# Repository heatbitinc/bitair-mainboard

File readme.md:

# Heatbit Bitair Mainboard

The mining mainboard of the Heatbit Bitair air purifier. It carries a single
Bitmain **BM1370** Bitcoin mining ASIC and an **ESP32-S3**, and the heat from
the ASIC is used by the purifier.

The design is based on the open source
[bitaxeGamma](https://github.com/bitaxeorg/bitaxeGamma) by bitaxeorg. See [NOTICE.md](NOTICE.md) for the upstream revision
and the full list of changes.

## Status

| Revision | Date       | Status                         |
|----------|------------|--------------------------------|
| V1.22    | 2026-08-24 | Production, shipped in Bitair  |
| V1.11    | 2026-07-31 | Internal, debugging only       |
| V1.00    | 2026-07-10 | Internal, debugging only       |

See [CHANGELOG.md](CHANGELOG.md).

## Overview

- ASIC: Bitmain BM1370 (the chip used in the Antminer S21 Pro). It is not
  open source and is not sold individually. Upstream reports about
  1.2 TH/s per chip.
- Core power: TI TPS546D24A step-down converter for the ASIC core (VDD),
  same as bitaxeGamma.
- 5 V rail: an on-board step-down converter from the CN1 input (sheet
  `Power_15_5`, NDP1415QF controller).
- MCU: ESP32-S3-WROOM-1 (N16R8).
- Fan control and ASIC temperature: Microchip EMC2101.
- PCB: 4 layers, about 72.5 × 80.5 mm. KiCad 10 (the files no longer open in KiCad 9).

**Active cooling is mandatory.** The board is designed to run with the
purifier's heatsink and airflow. Running it without them will overheat the
ASIC.

## Connectors

### CN1: system connector (JST B10B-PHDSS, 2 mm, 10 pins)

This connector links the board to the rest of the air purifier.

| Pin | Net       | Description |
|-----|-----------|-------------|
| 1   | VBUS      | Power input. 15 V nominal; the input converter enables at about 12 V (see the notes on sheet `Power_15_5`). Protected by fuse F1 (3 A). |
| 2   | VBUS      | Power input, same as pin 1 |
| 3   | GND       | Ground |
| 4   | GND       | Ground |
| 5   | SCL (ext) | I2C clock for an external sensor (AHT20). Level-shifted by Q4 (2N7002) from the 3.3 V bus. Needs a pull-up on the external side. |
| 6   | LED       | ESP32 GPIO41, 3.3 V logic, direct |
| 7   | SDA (ext) | I2C data for an external sensor. Level-shifted by Q5 (2N7002). Needs a pull-up on the external side. |
| 8   | FAN       | ESP32 GPIO40 through the level shifter Q3 (2N7002, 5.1 kΩ pull-up to 3.3 V on the ESP32 side). Pulled low when GPIO40 is low; needs a pull-up on the external side. |
| 9   | B         | ESP32 GPIO39, 3.3 V logic, direct |
| 10  | FAN_PWM   | Fan PWM from the EMC2101, 10 kΩ pull-up to 5 V |

The ESP32 measures the VBUS voltage on GPIO6 through a 51 kΩ / 12 kΩ divider.

### J5: USB-C

USB 2.0 data to the ESP32-S3, used for flashing and logs. USB VBUS is **not
connected**: the board cannot be powered from USB.

### J1: programming header (not populated)

A 1.27 mm, 6-pin footprint: 3V3, TX, RX, GND, IO0, EN (ESP32 UART0 and boot).

## Repository contents

| Path | Contents |
|------|----------|
| `bitair-mainboard.kicad_pro` | KiCad 10 project |
| `*.kicad_sch` | Schematic: root sheet, `bm1370`, `power`, `Power_15_5`, `esp32`, `fan` |
| `bitair-mainboard.kicad_pcb` | PCB |
| `bitaxe.kicad_sym`, `bitaxe.pretty` | Symbol and footprint libraries from upstream bitaxe |
| `bitair.kicad_sym`, `bitair.pretty`, `Heatbit.kicad_sym`, `Heatbit.pretty` | Libraries added by Heatbit |
| `3d`, `3dshapes` | 3D models used by the PCB, see [THIRD_PARTY.md](THIRD_PARTY.md) |
| `OUTPUTS/` | Fabrication outputs for V1.22: Gerbers and drill files, BOM, pick-and-place, schematic PDF |

## Manufacturing

- Gerbers and drill files: `OUTPUTS/HB Bitair MainBoard V1.22 GBR/`
- BOM: `OUTPUTS/Assembly/BOM/` (xlsx and csv). The `LCSC` column lists the
  parts used in production. `Manufacturer`/`MPN` are filled where known.
  `Alt MPN`/`DigiKey` are the alternatives inherited from bitaxeGamma for
  parts that did not change.
- Pick-and-place: `OUTPUTS/Assembly/PnP/`
- Schematic PDF: `OUTPUTS/Assembly/Circuit Diagram/`

The BM1370 is not available from regular distributors.

See [building.md](building.md) for generating fabrication files and
[assembly.md](assembly.md) for hand-assembly tips from the bitaxe project.

## Firmware

The firmware is not part of this repository.

## Licence

Copyright (c) 2026 Heatbit Inc. Based on bitaxeGamma, copyright (c)
bitaxeorg.

This design is licensed under the
[CERN-OHL-S-2.0](LICENSE). If you distribute boards or modified designs based
on it, you must make your complete modified source available under the same
licence.

"Heatbit", "Bitair" and the Heatbit logo are trademarks of Heatbit Inc. and
are not covered by the licence. See [TRADEMARKS.md](TRADEMARKS.md) before
manufacturing boards from this design. Bitaxe is a trademark of bitaxeorg;
this is not an official Bitaxe product.

Third-party components and 3D models are listed in
[THIRD_PARTY.md](THIRD_PARTY.md).

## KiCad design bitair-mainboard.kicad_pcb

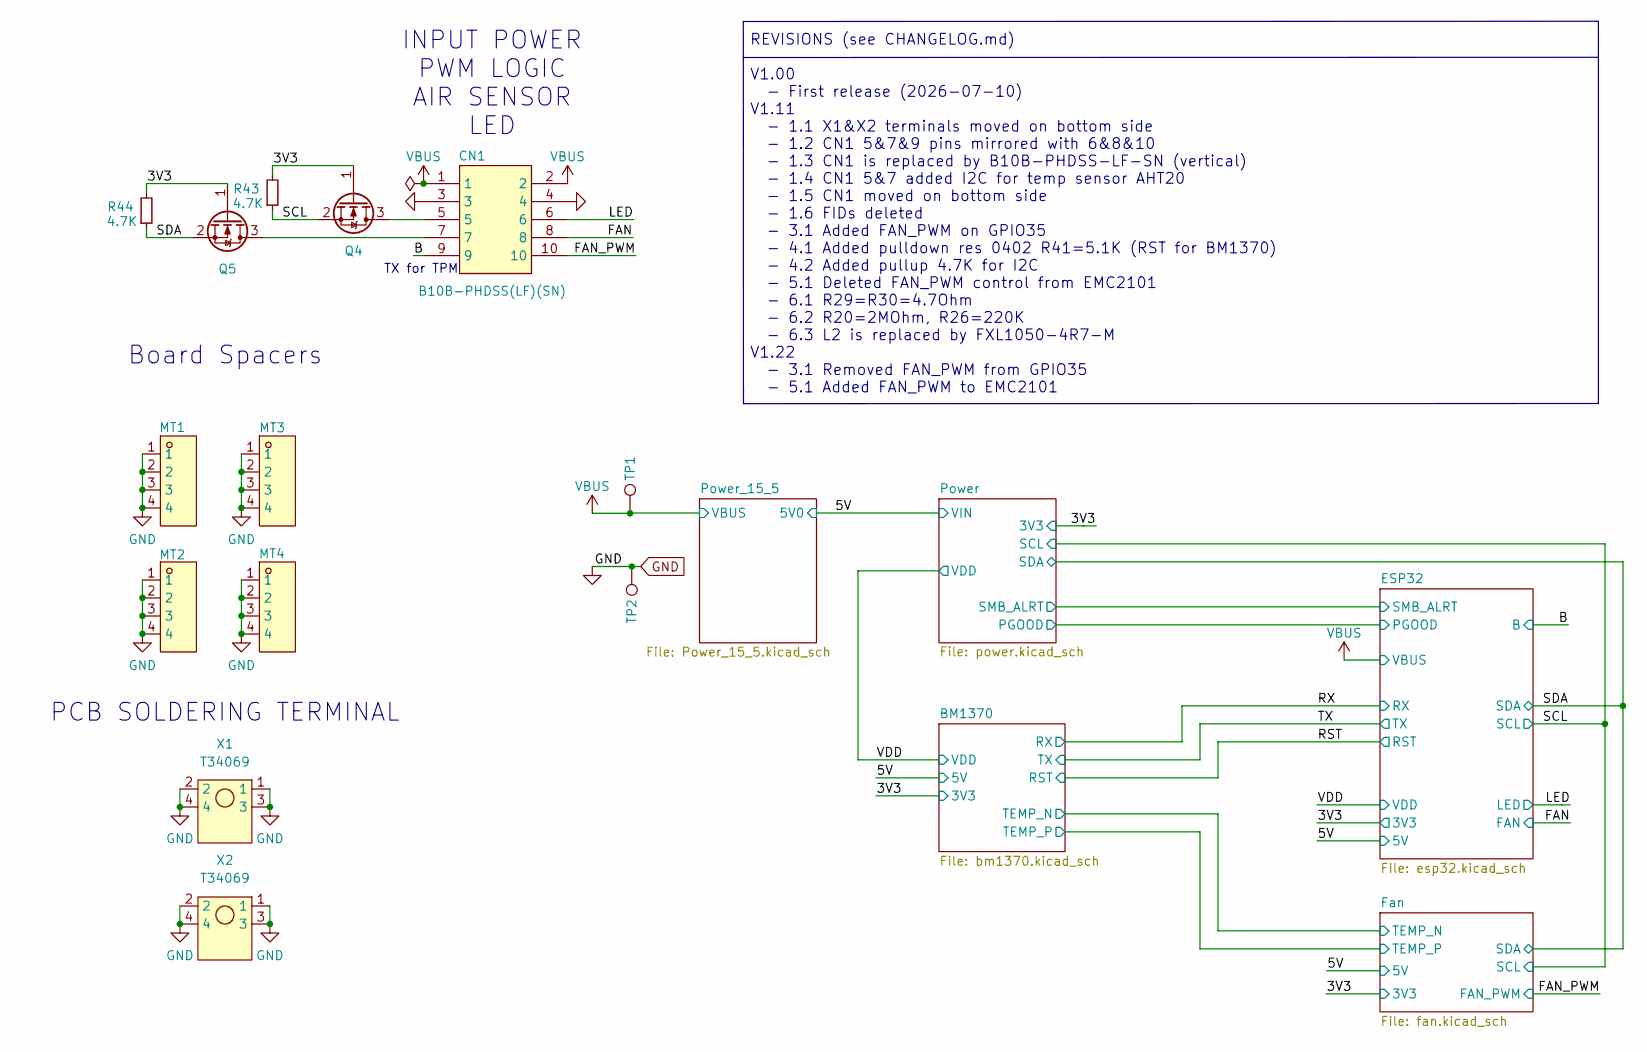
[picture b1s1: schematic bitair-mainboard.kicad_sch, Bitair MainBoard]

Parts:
CN1: B10B-PHDSS(LF)(SN); CONN-TH_B10B-PHDSS-LF-SN; MPN B10B-PHDSS(LF)(SN); LCSC C471519
MT1, MT2, MT3, MT4: SMTSO3025CTJ; SMD_BD5.6-D4.1; MPN SMTSO3025CTJ; LCSC C2916365
Q4, Q5: 2N7002E; SOT-23; MPN 2N7002ET1G; LCSC C71533
R43, R44: 4.7K; R_0402_1005Metric; LCSC C2906869
TP1, TP2: TestPoint; TestPoint_Pad_D1.5mm
X1, X2: T34069; XFCN_PKT-TH_4P-T34069; MPN T34069; LCSC C481452

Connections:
/3V3: Q4.1 (G), Q5.1 (G), R43.2, R44.2; also elsewhere on the board
/B: CN1.9; also elsewhere on the board
/FAN: CN1.8; also elsewhere on the board
/FAN_PWM: CN1.10; also elsewhere on the board
/LED: CN1.6; also elsewhere on the board
/SCL: Q4.2 (S), R43.1; also elsewhere on the board
/SDA: Q5.2 (S), R44.1; also elsewhere on the board
GND: CN1.3, CN1.4, MT1.1, MT1.2, MT1.3, MT1.4, MT2.1, MT2.2, MT2.3, MT2.4, MT3.1, MT3.2, MT3.3, MT3.4, MT4.1, MT4.2, MT4.3, MT4.4, TP2.1 (1_1), X1.1, X1.2, X1.3, X1.4, X2.1, X2.2, X2.3, X2.4; also elsewhere on the board
unnamed: CN1.5, Q4.3 (D)
unnamed: CN1.7, Q5.3 (D)
VBUS: CN1.1, CN1.2, TP1.1 (1_1); also elsewhere on the board

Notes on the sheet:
Board Spacers
PCB SOLDERING TERMINAL
INPUT POWER PWM LOGIC AIR SENSOR LED
REVISIONS (see CHANGELOG.md) V1.00 - First release (2026-07-10) V1.11 - 1.1 X1&X2 terminals moved on bottom side - 1.2 CN1 5&7&9 pins mirrored with 6&8&10 - 1.3 CN1 is replaced by B10B-PHDSS-LF-SN (vertical) - 1.4 CN1 5&7 added I2C for temp sensor AHT20 - 1.5 CN1 moved on bottom side - 1.6 FIDs del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
TX for TPM

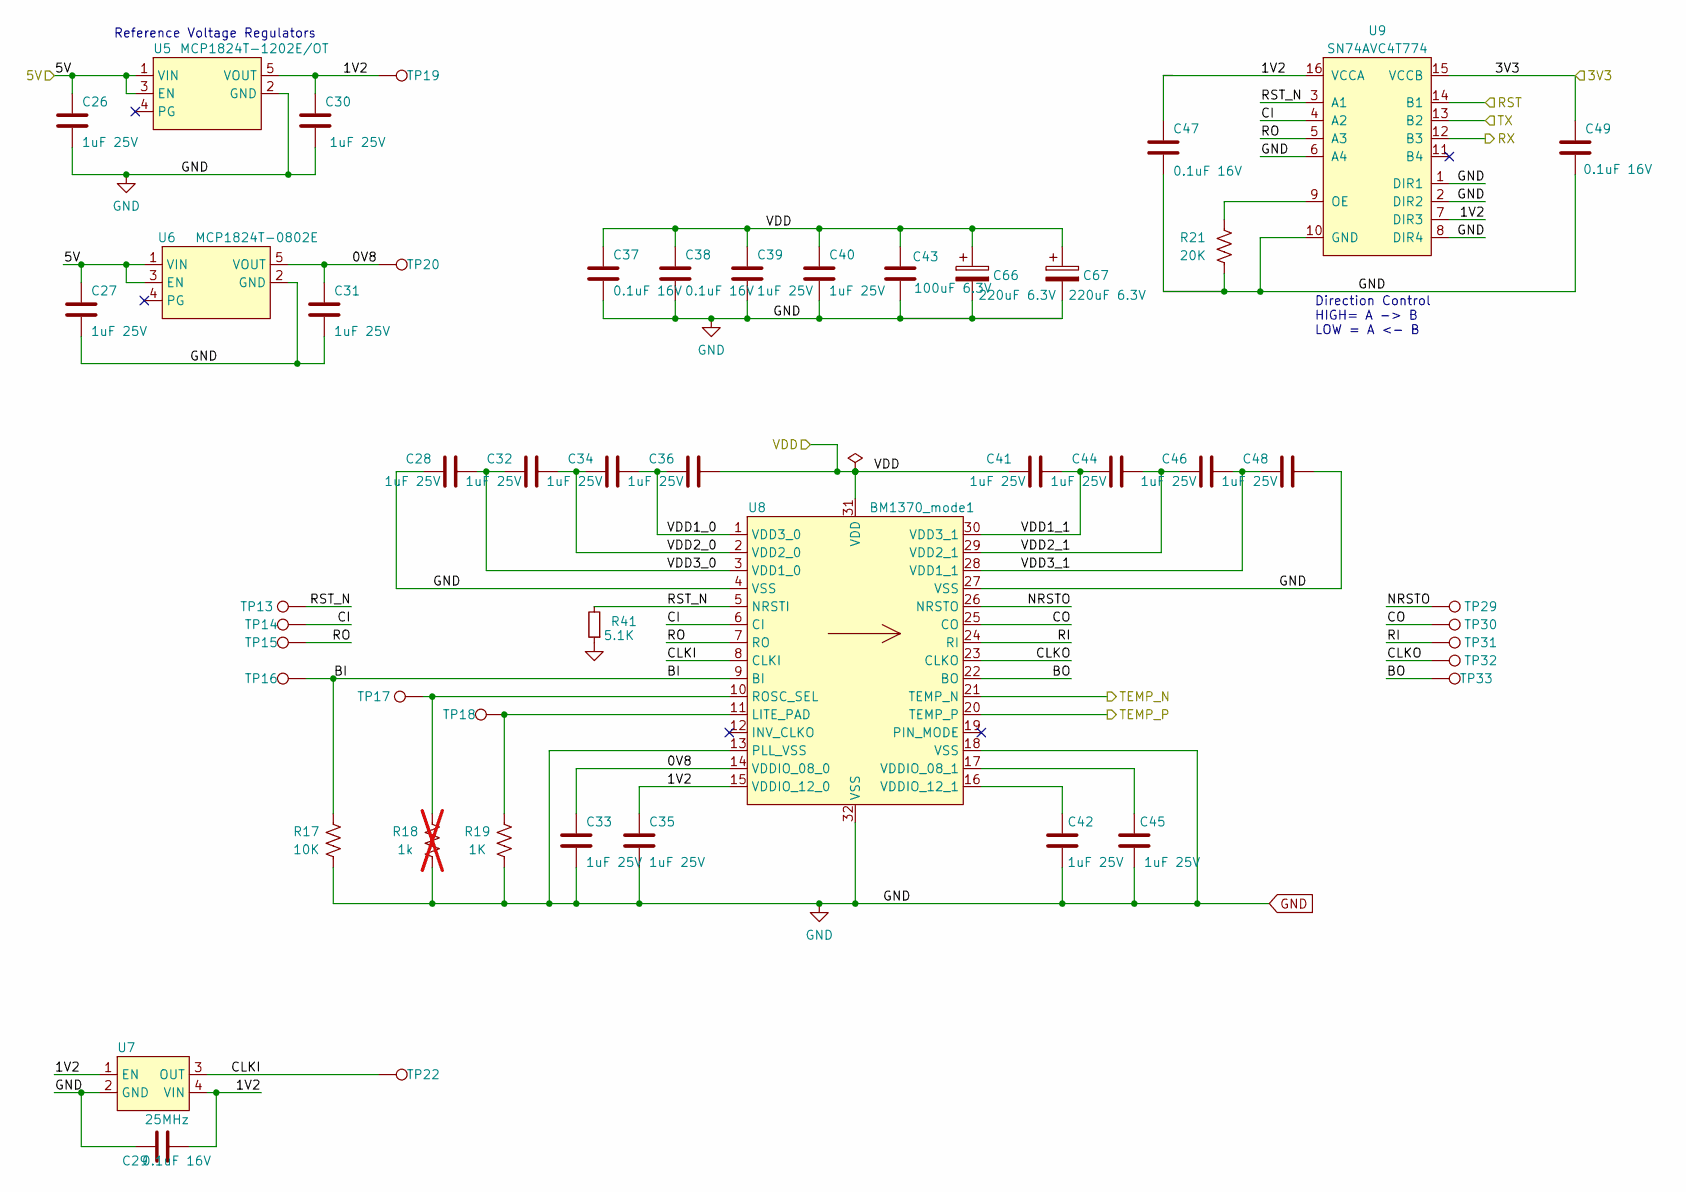
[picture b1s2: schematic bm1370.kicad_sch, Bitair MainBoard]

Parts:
C26, C27, C28, C30, C31, C32, C33, C34, C35, C36, C39, C40, C41, C42, C44, C45, C46, C48: 1uF 25V; C_0402_1005Metric; LCSC C7467048
C29, C37, C38, C47, C49: 0.1uF 16V; C_0402_1005Metric; DigiKey 1276-1234-1-ND
C43: 100uF 6.3V; C_1206_3216Metric; DigiKey 1276-1782-1-ND
C66, C67: 220uF 6.3V; CAP-SMD_L3.5-W2.8-R-RD; MPN 6TPE220MAZB; LCSC C79111
R17: 10K; R_0402_1005Metric; DigiKey 311-10KJRCT-ND
R18: 1k; R_0402_1005Metric; DigiKey 311-1.00KLRCT-ND; not fitted
R19: 1K; R_0402_1005Metric; DigiKey 311-1.00KLRCT-ND
R21: 20K; R_0402_1005Metric; DigiKey 311-20.0KLRCT-ND
R41: 5.1K; R_0402_1005Metric; LCSC C2906874
TP13, TP14, TP15, TP16, TP17, TP18, TP19, TP20, TP22, TP29, TP30, TP31, TP32, TP33: TestPoint; TestPoint_Pad_D1.5mm
U5: MCP1824T-1202E/OT; SOT-23-5; MPN MCP1824T-1202E/OT; DigiKey MCP1824T-1202E/OTCT-ND
U6: MCP1824T-0802E; SOT-23-5; MPN MCP1824T-0802E/OT; DigiKey MCP1824T-0802E/OTCT-ND
U7: 25MHz; SMD3225-4P; MPN SX3M25.000E20F30THN; LCSC C5137262
U8: BM1370_mode1; BM1370; MPN BM1370
U9: SN74AVC4T774; TSSOP-16_4.4x5mm_P0.65mm; MPN SN74AVC4T774PWR; DigiKey 296-24739-1-ND

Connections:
5V0: C26.1, C27.1, U5.1 (VIN), U5.3 (EN), U6.1 (VIN), U6.3 (EN); also elsewhere on the board
/3V3: C49.1, U9.15 (VCCB); also elsewhere on the board
/BM1370/0V8: C31.1, C33.1, TP20.1 (1_1), U6.5 (VOUT), U8.14 (VDDIO_08_0)
/BM1370/1V2: C29.2, C30.1, C35.1, C47.1, TP19.1 (1_1), U5.5 (VOUT), U7.1 (EN), U7.4 (VIN), U8.15 (VDDIO_12_0), U9.7 (DIR3), U9.16 (VCCA)
/BM1370/BI: R17.2, TP16.1 (1_1), U8.9 (BI)
/BM1370/BO: TP33.1 (1_1), U8.22 (BO)
/BM1370/CI: TP14.1 (1_1), U8.6 (CI), U9.4 (A2)
/BM1370/CLKI: TP22.1 (1_1), U7.3 (OUT), U8.8 (CLKI)
/BM1370/CLKO: TP32.1 (1_1), U8.23 (CLKO)
/BM1370/CO: TP30.1 (1_1), U8.25 (CO)
/BM1370/NRSTO: TP29.1 (1_1), U8.26 (NRSTO)
/BM1370/RI: TP31.1 (1_1), U8.24 (RI)
/BM1370/RO: TP15.1 (1_1), U8.7 (RO), U9.5 (A3)
/BM1370/RST_N: R41.2, TP13.1 (1_1), U8.5 (NRSTI), U9.3 (A1)
/BM1370/VDD1_0: C34.2, C36.1, U8.1 (VDD3_0)
/BM1370/VDD1_1: C41.2, C44.1, U8.30 (VDD3_1)
/BM1370/VDD2_0: C32.2, C34.1, U8.2 (VDD2_0)
/BM1370/VDD2_1: C44.2, C46.1, U8.29 (VDD2_1)
/BM1370/VDD3_0: C28.2, C32.1, U8.3 (VDD1_0)
/BM1370/VDD3_1: C46.2, C48.1, U8.28 (VDD1_1)
/Fan/TEMP_N: U8.21 (TEMP_N); also elsewhere on the board
/Fan/TEMP_P: U8.20 (TEMP_P); also elsewhere on the board
/RST: U9.14 (B1); also elsewhere on the board
/RX: U9.12 (B3); also elsewhere on the board
/TX: U9.13 (B2); also elsewhere on the board
/VDD: C36.2, C37.1, C38.1, C39.1, C40.1, C41.1, C43.1, C66.1, C67.1, U8.31 (VDD); also elsewhere on the board
GND: C26.2, C27.2, C28.1, C29.1, C30.2, C31.2, C33.2, C35.2, C37.2, C38.2, C39.2, C40.2, C42.2, C43.2, C45.2, C47.2, C48.2, C49.2, C66.2, C67.2, R17.1, R18.1, R19.1, R21.1, R41.1, U5.2 (GND), U6.2 (GND), U7.2 (GND), U8.4 (VSS), U8.13 (PLL_VSS), U8.18 (VSS), U8.27 (VSS), U8.32 (VSS), U9.1 (DIR1), U9.2 (DIR2), U9.6 (A4), U9.8 (DIR4), U9.10 (GND); also elsewhere on the board
unnamed: R19.2, TP18.1 (1_1), U8.11 (LITE_PAD)
unnamed: R18.2, TP17.1 (1_1), U8.10 (ROSC_SEL)
unnamed: C45.1, U8.17 (VDDIO_08_1)
unnamed: C42.1, U8.16 (VDDIO_12_1)
unnamed: R21.2, U9.9 (OE)

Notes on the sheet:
Reference Voltage Regulators
Direction Control HIGH= A -> B LOW = A <- B

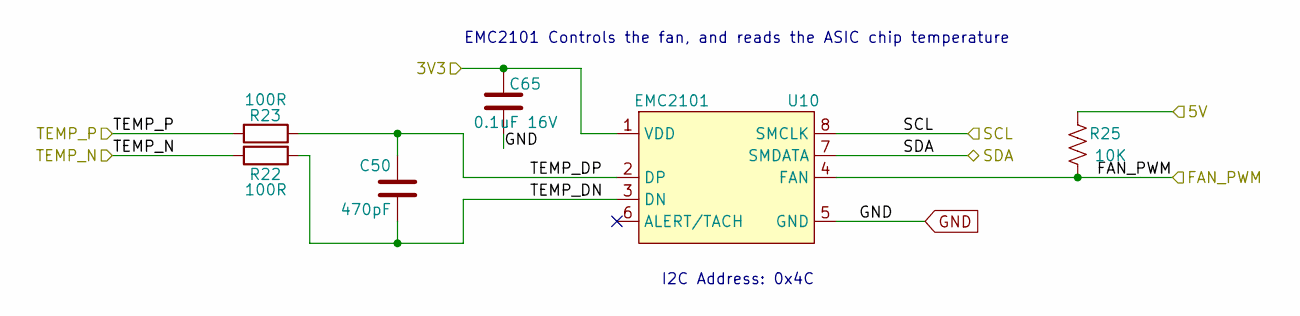
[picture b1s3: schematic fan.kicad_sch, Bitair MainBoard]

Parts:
C50: 470pF; C_0402_1005Metric; DigiKey 1276-1566-1-ND
C65: 0.1uF 16V; C_0402_1005Metric; LCSC C159816
R22, R23: 100R; R_0402_1005Metric; LCSC C144808
R25: 10K; R_0402_1005Metric; DigiKey 311-10KJRCT-ND
U10: EMC2101; TSSOP-8_3x3mm_P0.65mm; MPN EMC2101-R-ACZL-TR; DigiKey EMC2101-R-ACZL-CT-ND

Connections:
5V0: R25.2; also elsewhere on the board
/3V3: C65.1, U10.1 (VDD); also elsewhere on the board
/FAN_PWM: R25.1, U10.4 (FAN); also elsewhere on the board
/Fan/TEMP_DN: C50.2, R22.1, U10.3 (DN)
/Fan/TEMP_DP: C50.1, R23.1, U10.2 (DP)
/Fan/TEMP_N: R22.2; also elsewhere on the board
/Fan/TEMP_P: R23.2; also elsewhere on the board
/SCL: U10.8 (SMCLK); also elsewhere on the board
/SDA: U10.7 (SMDATA); also elsewhere on the board
GND: C65.2, U10.5 (GND); also elsewhere on the board

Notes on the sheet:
EMC2101 Controls the fan, and reads the ASIC chip temperature
I2C Address: 0x4C

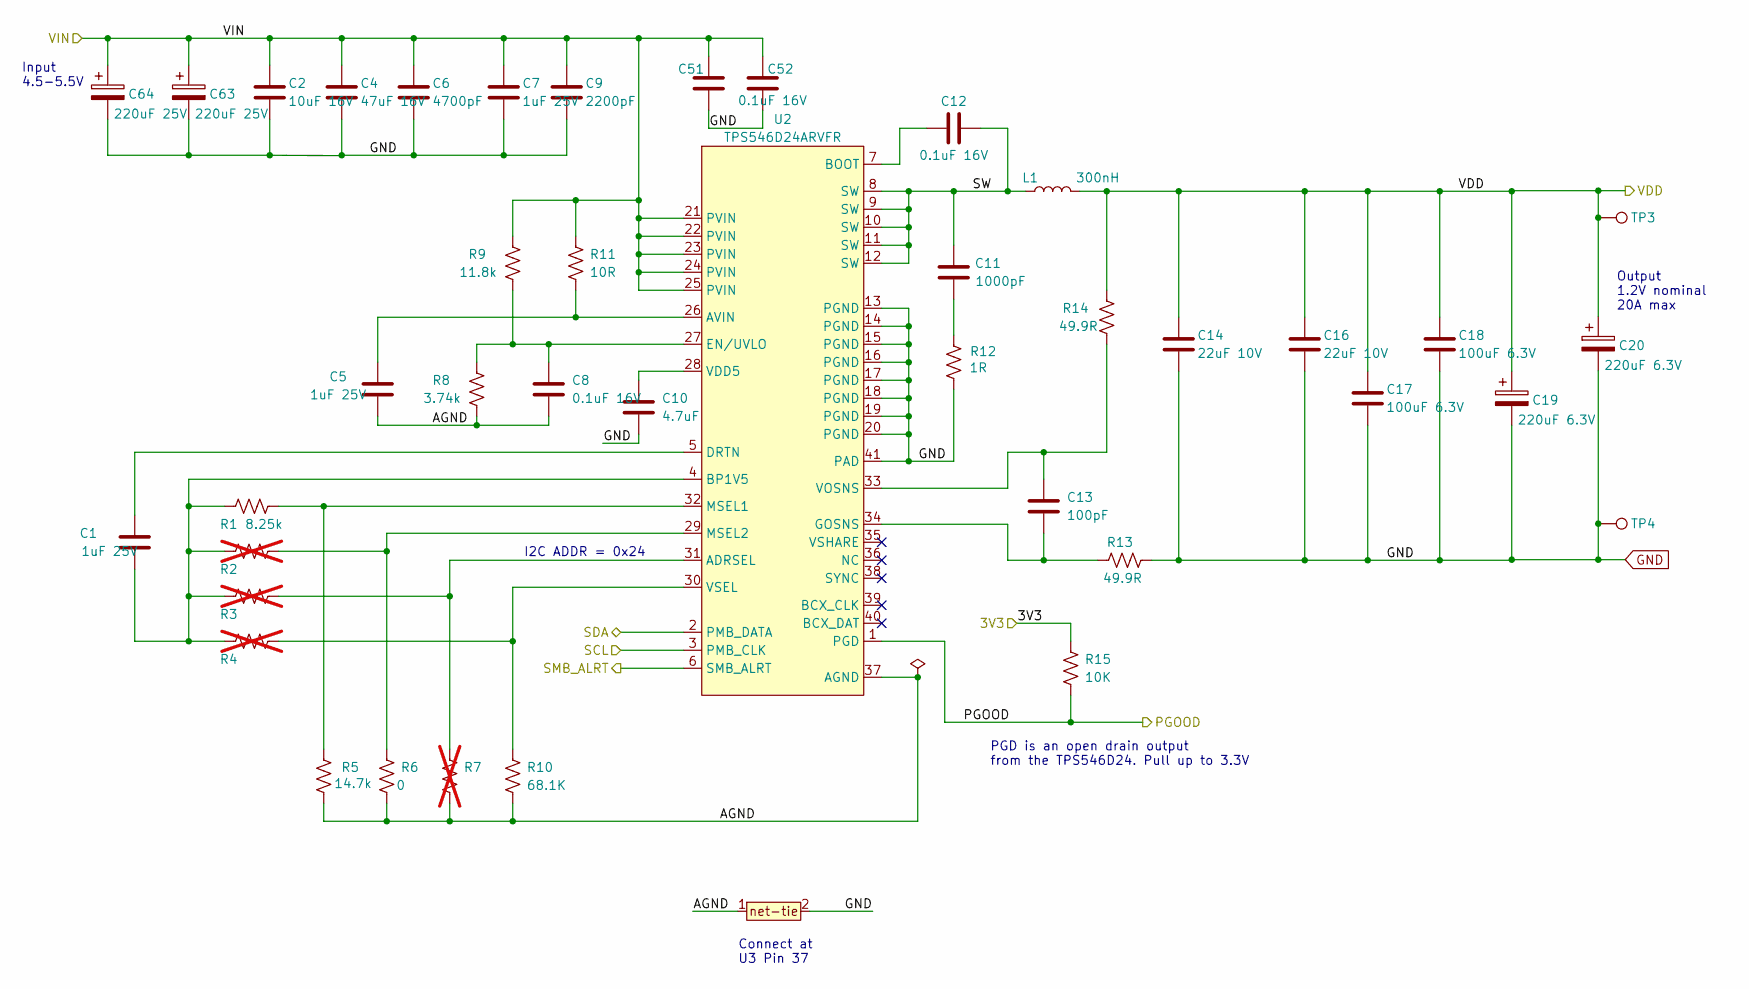
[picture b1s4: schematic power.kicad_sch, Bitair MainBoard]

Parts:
C1, C5, C7: 1uF 25V; C_0402_1005Metric; LCSC C7467048
C2: 10uF 16V; C_0805_2012Metric; DigiKey 1276-1096-1-ND
C4, C51: 47uF 16V; C_1210_3225Metric; DigiKey 1276-3376-1-ND
C6: 4700pF; C_0402_1005Metric; DigiKey 490-1309-1-ND
C8, C12, C52: 0.1uF 16V; C_0402_1005Metric; DigiKey 1276-1234-1-ND
C9: 2200pF; C_0402_1005Metric; DigiKey 490-8257-1-ND
C10: 4.7uF; C_0402_1005Metric; DigiKey 490-14306-1-ND
C11: 1000pF; C_0805_2012Metric; DigiKey 311-1127-1-ND
C13: 100pF; C_0402_1005Metric; DigiKey 732-7431-1-ND
C14, C16: 22uF 10V; C_0805_2012Metric; DigiKey 490-10746-1-ND
C17, C18: 100uF 6.3V; C_1206_3216Metric; DigiKey 1276-1782-1-ND
C19, C20: 220uF 6.3V; CAP-SMD_L3.5-W2.8-R-RD; MPN 6TPE220MAZB; LCSC C79111
C63, C64: 220uF 25V; CP_Elec_6.3x7.9; MPN JVJ25V220M6x8; LCSC C51018389
L1: 300nH; SLC1175-271MEC_COC; MPN FP1007R3-R30-R; LCSC C2638821
R1: 8.25k; R_0402_1005Metric; DigiKey 311-8.25KLRCT-ND
R2, R3, R4, R7: R_0402_1005Metric; not fitted
R5: 14.7k; R_0402_1005Metric; DigiKey YAG2984CT-ND
R6: 0; R_0402_1005Metric; DigiKey 311-0.0JRCT-ND
R8: 3.74k; R_0402_1005Metric; DigiKey 311-3.74KLRCT-ND
R9: 11.8k; R_0402_1005Metric; DigiKey YAG2958CT-ND
R10: 68.1K; R_0402_1005Metric; DigiKey YAG3213CT-ND
R11: 10R; R_0402_1005Metric; DigiKey 311-10.0LRCT-ND
R12: 1R; R_1206_3216Metric; DigiKey CSR1206FT1R00CT-ND
R13, R14: 49.9R; R_0402_1005Metric; DigiKey 311-49.9LRCT-ND
R15: 10K; R_0402_1005Metric; DigiKey 311-10KJRCT-ND
T1: net-tie; NetTie-0.25mm
TP3, TP4: TestPoint; TestPoint_Pad_D1.5mm
U2: TPS546D24ARVFR; LQFN40-CLIP; MPN TPS546D24ARVFR; DigiKey 296-TPS546D24ARVFRCT-ND

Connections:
5V0: C2.1, C4.1, C6.1, C7.1, C9.1, C51.1, C52.1, C63.1, C64.1, R9.1, R11.1, U2.21 (PVIN), U2.22 (PVIN), U2.23 (PVIN), U2.24 (PVIN), U2.25 (PVIN); also elsewhere on the board
/3V3: R15.2; also elsewhere on the board
/ESP32/SMB_ALRT: U2.6 (SMB_ALRT); also elsewhere on the board
/Power/AGND: C5.1, C8.2, R5.1, R6.2, R7.2, R8.2, R10.2, T1.1, U2.37 (AGND)
/Power/PGOOD: R15.1, U2.1 (PGD); also elsewhere on the board
/Power/SW: C11.2, C12.2, L1.1, U2.8 (SW), U2.9 (SW), U2.10 (SW), U2.11 (SW), U2.12 (SW)
/SCL: U2.3 (PMB_CLK); also elsewhere on the board
/SDA: U2.2 (PMB_DATA); also elsewhere on the board
/VDD: C14.1, C16.1, C17.1, C18.1, C19.1, C20.1, L1.2, R14.1, TP3.1 (1_1); also elsewhere on the board
GND: C2.2, C4.2, C6.2, C7.2, C9.2, C10.2, C14.2, C16.2, C17.2, C18.2, C19.2, C20.2, C51.2, C52.2, C63.2, C64.2, R12.1, R13.2, T1.2, TP4.1 (1_1), U2.13 (PGND), U2.14 (PGND), U2.15 (PGND), U2.16 (PGND), U2.17 (PGND), U2.18 (PGND), U2.19 (PGND), U2.20 (PGND), U2.41 (PAD); also elsewhere on the board
unnamed: C11.1, R12.2
unnamed: R3.2, R7.1, U2.31 (ADRSEL)
unnamed: C5.2, R11.2, U2.26 (AVIN)
unnamed: C12.1, U2.7 (BOOT)
unnamed: C1.2, R1.1, R2.1, R3.1, R4.1, U2.4 (BP1V5)
unnamed: C1.1, U2.5 (DRTN)
unnamed: C8.1, R8.1, R9.2, U2.27 (EN/UVLO)
unnamed: C13.2, R13.1, U2.34 (GOSNS)
unnamed: R1.2, R5.2, U2.32 (MSEL1)
unnamed: R2.2, R6.1, U2.29 (MSEL2)
unnamed: C10.1, U2.28 (VDD5)
unnamed: C13.1, R14.2, U2.33 (VOSNS)
unnamed: R4.2, R10.1, U2.30 (VSEL)

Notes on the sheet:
Input 4.5-5.5V
PGD is an open drain output from the TPS546D24. Pull up to 3.3V
I2C ADDR = 0x24
Output 1.2V nominal 20A max
Connect at U3 Pin 37

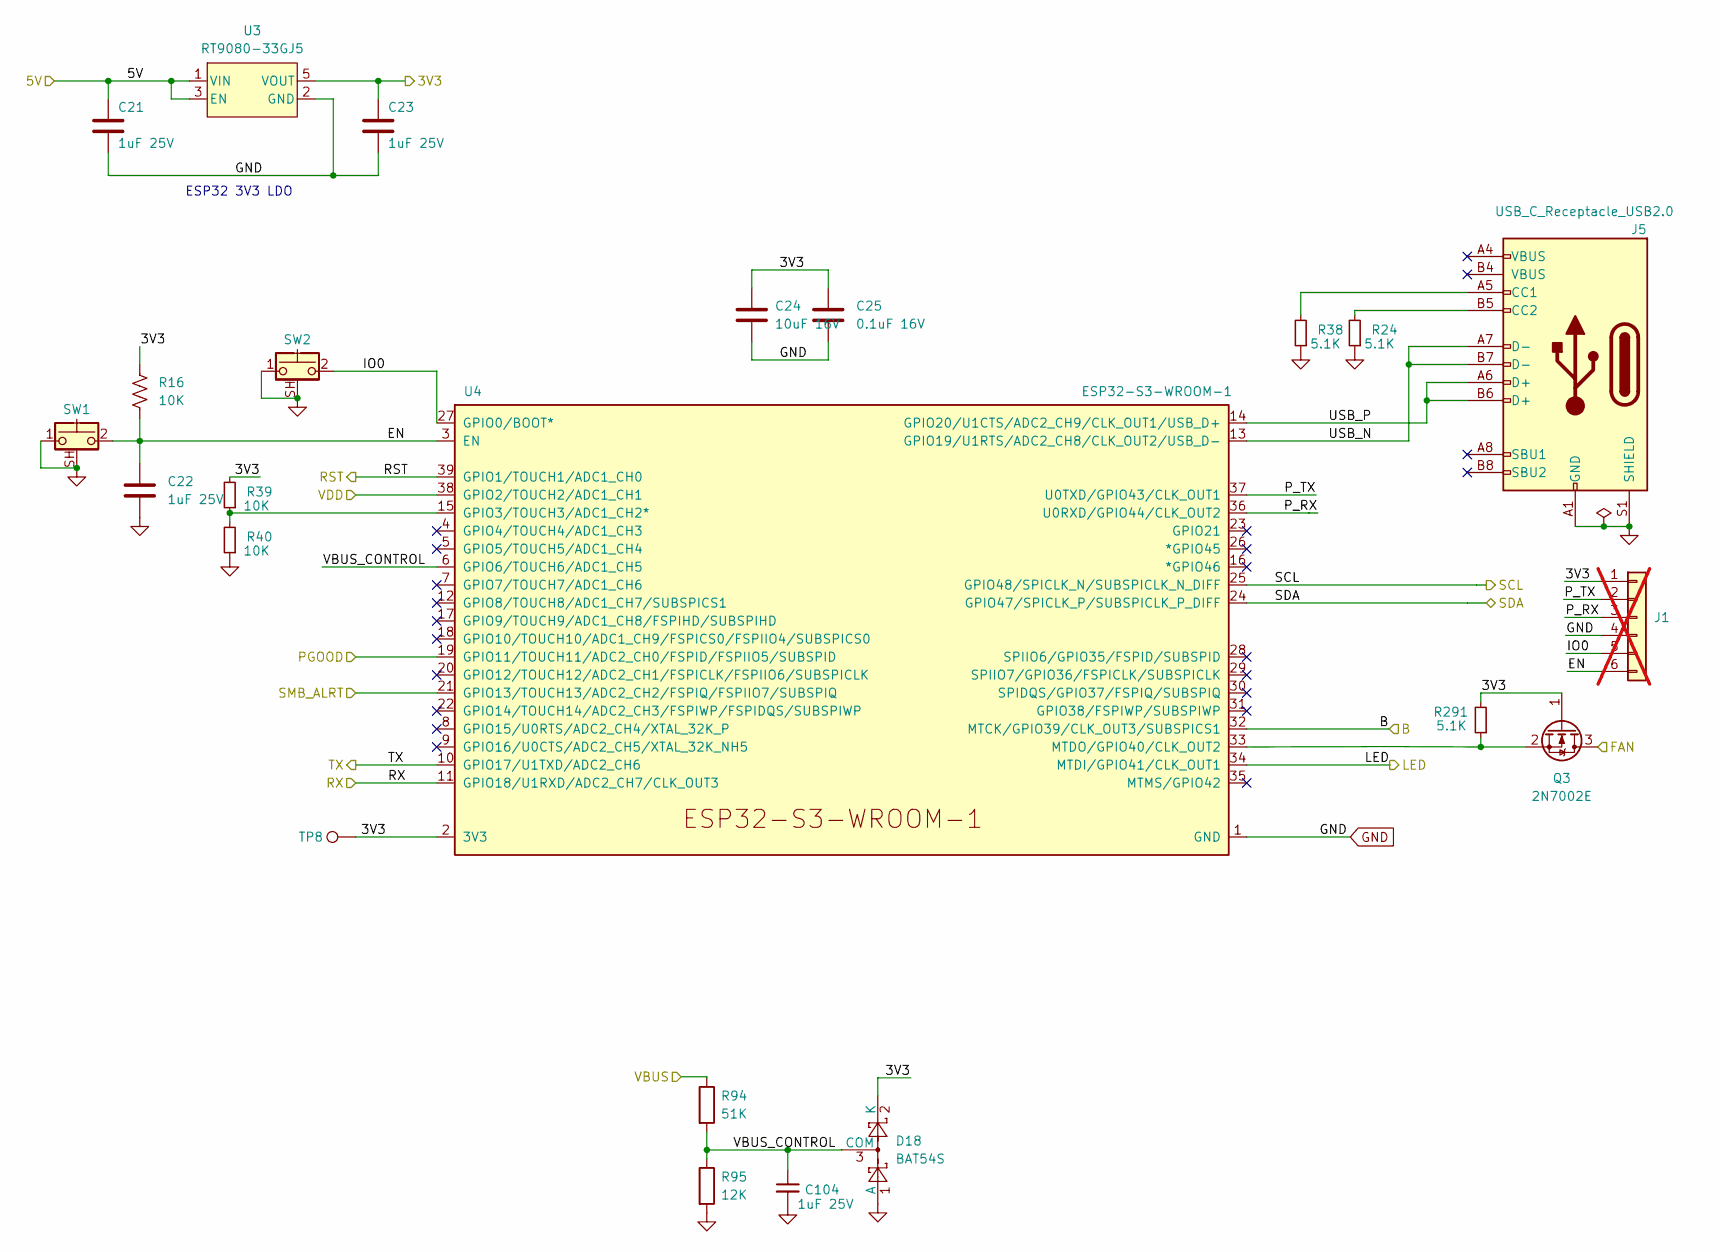
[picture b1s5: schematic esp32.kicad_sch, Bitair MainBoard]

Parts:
C21, C22, C23, C104: 1uF 25V; C_0402_1005Metric; LCSC C7467048
C24: 10uF 16V; C_0805_2012Metric; DigiKey 1276-1096-1-ND
C25: 0.1uF 16V; C_0402_1005Metric; DigiKey 1276-1234-1-ND
D18: BAT54S; SOT-23; MPN BAT54S; LCSC C19726
J1: Conn_01x06; PinHeader_1x06_P1.27mm_Vertical; MPN PZ254V-11-06P; LCSC C492405; not fitted
J5: USB_C_Receptacle_USB2.0; USB_C_Receptacle_GCT_USB4105-xx-A; MPN USB4105-GF-A; DigiKey 2073-USB4105-GF-ACT-ND
Q3: 2N7002E; SOT-23; MPN 2N7002ET1G; LCSC C71533
R16: 10K; R_0402_1005Metric; DigiKey 311-10KJRCT-ND
R24, R38, R291: 5.1K; R_0402_1005Metric; LCSC C2906874
R39, R40: 10K; R_0402_1005Metric; LCSC C60490
R94: 51K; R_0402_1005Metric; LCSC C409055
R95: 12K; R_0402_1005Metric; LCSC C2692918
SW1, SW2: CK_KMS2xxG; SW_SPST_CK_KMS2xxGP; MPN KMS231GLFS; LCSC C221703
TP8: TestPoint; TestPoint_Pad_D1.5mm
U3: RT9080-33GJ5; MPN RT9080-33GJ5; DigiKey 1028-1509-1-ND
U4: ESP32-S3-WROOM-1; MPN ESP32-S3-WROOM-1-N16R8; DigiKey 1965-ESP32-S3-WROOM-1-N16R8CT-ND

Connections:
5V0: C21.1, U3.1 (VIN), U3.3 (EN); also elsewhere on the board
/3V3: C23.1, C24.1, C25.1, D18.2 (K), J1.1, Q3.1 (G), R16.1, R39.2, R291.2, TP8.1 (1_1), U3.5 (VOUT), U4.2 (3V3); also elsewhere on the board
/B: U4.32 (MTCK/GPIO39/CLK_OUT3/SUBSPICS1); also elsewhere on the board
/ESP32/EN: C22.1, J1.6, R16.2, SW1.2, U4.3 (EN)
/ESP32/IO0: J1.5, SW2.2, U4.27 (GPIO0/BOOT*)
/ESP32/P_RX: J1.3, U4.36 (U0RXD/GPIO44/CLK_OUT2)
/ESP32/P_TX: J1.2, U4.37 (U0TXD/GPIO43/CLK_OUT1)
/ESP32/SMB_ALRT: U4.21 (GPIO13/TOUCH13/ADC2_CH2/FSPIQ/FSPIIO7/S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); also elsewhere on the board
/ESP32/USB_N: J5.A7 (D-), J5.B7 (D-), U4.13 (GPIO19/U1RTS/ADC2_CH8/CLK_OUT2/USB_D-)
/ESP32/USB_P: J5.A6 (D+), J5.B6 (D+), U4.14 (GPIO20/U1CTS/ADC2_CH9/CLK_OUT1/USB_D+)
/ESP32/VBUS_CONTROL: C104.1, D18.3 (COM), R94.2, R95.1, U4.6 (GPIO6/TOUCH6/ADC1_CH5)
/FAN: Q3.3 (D); also elsewhere on the board
/LED: U4.34 (MTDI/GPIO41/CLK_OUT1); also elsewhere on the board
/Power/PGOOD: U4.19 (GPIO11/TOUCH11/ADC2_CH0/FSPID/FSPIIO5/S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); also elsewhere on the board
/RST: U4.39 (GPIO1/TOUCH1/ADC1_CH0); also elsewhere on the board
/RX: U4.11 (GPIO18/U1RXD/ADC2_CH7/CLK_OUT3); also elsewhere on the board
/SCL: U4.25 (GPIO48/SPICLK_N/SUBSPICLK_N_DIFF); also elsewhere on the board
/SDA: U4.24 (GPIO47/SPICLK_P/SUBSPICLK_P_DIFF); also elsewhere on the board
/TX: U4.10 (GPIO17/U1TXD/ADC2_CH6); also elsewhere on the board
/VDD: U4.38 (GPIO2/TOUCH2/ADC1_CH1); also elsewhere on the board
GND: C21.2, C22.2, C23.2, C24.2, C25.2, C104.2, D18.1 (A), J1.4, J5.A1 (GND), J5.B1 (GND), J5.S1 (SHIELD), R24.1, R38.1, R40.1, R95.2, SW1.1, SW1.SH (B), SW2.1, SW2.SH (B), U3.2 (GND), U4.1 (GND), U4.40 (GND), U4.41 (GND); also elsewhere on the board
unnamed: J5.A5 (CC1), R38.2
unnamed: J5.B5 (CC2), R24.2
unnamed: Q3.2 (S), R291.1, U4.33 (MTDO/GPIO40/CLK_OUT2)
unnamed: R39.1, R40.2, U4.15 (GPIO3/TOUCH3/ADC1_CH2*)
VBUS: R94.1; also elsewhere on the board

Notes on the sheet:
ESP32 3V3 LDO

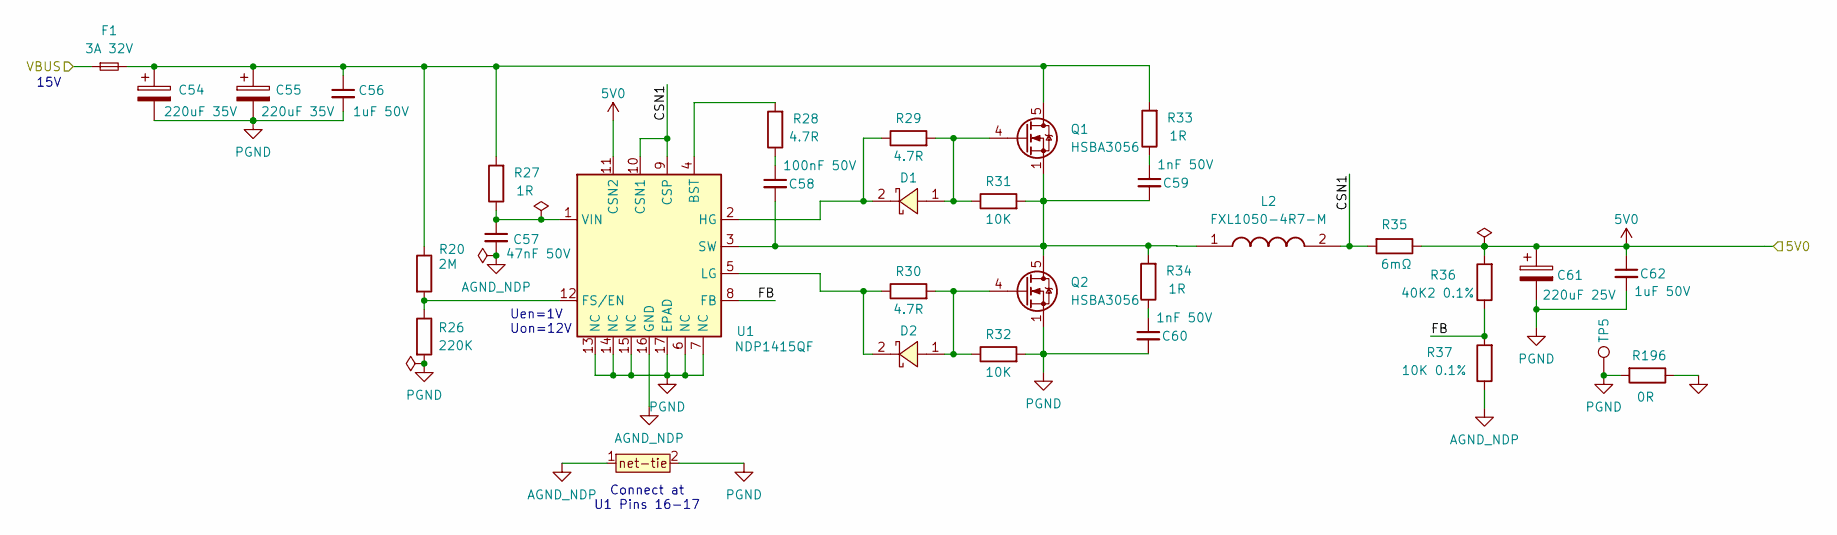
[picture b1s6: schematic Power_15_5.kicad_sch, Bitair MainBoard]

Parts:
C54, C55: 220uF 35V; CP_Elec_6.3x7.9; MPN JVJ35V220M6x8; LCSC C49256854
C56, C62: 1uF 50V; C_1206_3216Metric; LCSC C1848
C57: 47nF 50V; C_0805_2012Metric; LCSC C107154
C58: 100nF 50V; C_0603_1608Metric; LCSC C1591
C59, C60: 1nF 50V; C_0805_2012Metric; LCSC C94121
C61: 220uF 25V; CP_Elec_6.3x7.9; MPN JVJ25V220M6x8; LCSC C51018389
D1, D2: BAT46W; SOD-123_L2.7-W1.6-LS3.7-FD; MPN BAT46W; LCSC C7420332
F1: 3A 32V; Fuse_1206_3216Metric; MPN S1206-F-3.0A; LCSC C845163
L2: FXL1050-4R7-M; IND-SMD_L11.5-W10.0; MPN FXL1050-4R7-M; LCSC C5359261
Q1, Q2: HSBA3056; PRPAK-8_L5.1-W6.2-P1.27-LS6.1-BL; MPN HSBA3056; LCSC C701049
R20: 2M; R_0402_1005Metric; LCSC C138014
R26: 220K; R_0402_1005Metric; LCSC C2909335
R27: 1R; R_1206_3216Metric; LCSC C20476230
R28: 4.7R; R_0805_2012Metric; LCSC C2828871
R29, R30: 4.7R; R_0603_1608Metric; LCSC C2907035
R31, R32: 10K; R_0603_1608Metric; LCSC C98220
R33, R34: 1R; R_0805_2012Metric; LCSC C2907233
R35: 6mΩ; R_0805_2012Metric; MPN RLM10FTSMR006; LCSC C163092
R36: 40K2 0.1%; R_0603_1608Metric; LCSC C374525
R37: 10K 0.1%; R_0603_1608Metric; LCSC C95204
R196: 0R; R_1210_3225Metric; LCSC C2974058
T2: net-tie; NetTie-0.25mm
TP5: TestPoint; TestPoint_Pad_D1.5mm
U1: NDP1415QF; QFN-16_L3.0-W3.0-P0.50-BL-EP1.7; MPN NDP1415QF; LCSC C7420580

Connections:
5V0: C61.1, C62.1, R35.1, R36.2, U1.11 (CSN2); also elsewhere on the board
/Power_15_5/CSN1: L2.2, R35.2, U1.9 (CSP), U1.10 (CSN1)
/Power_15_5/FB: R36.1, R37.2, U1.8 (FB)
AGND_NDP: C57.2, R37.1, T2.1, U1.16 (GND)
GND: R196.1; also elsewhere on the board
unnamed: C54.1, C55.1, C56.1, F1.2, Q1.5 (D), Q1.6 (D), Q1.7 (D), Q1.8 (D), Q1.9 (D), R20.1, R27.2, R33.2
unnamed: C58.1, R28.1
unnamed: C59.1, R33.1
unnamed: C60.1, R34.1
unnamed: D1.1, Q1.4 (G), R29.2, R31.1
unnamed: D2.1, Q2.4 (G), R30.2, R32.1
unnamed: R28.2, U1.4 (BST)
unnamed: R20.2, R26.1, U1.12 (FS/EN)
unnamed: D1.2, R29.1, U1.2 (HG)
unnamed: D2.2, R30.1, U1.5 (LG)
unnamed: C58.2, C59.2, L2.1, Q1.1 (S), Q1.2 (S), Q1.3 (S), Q2.5 (D), Q2.6 (D), Q2.7 (D), Q2.8 (D), Q2.9 (D), R31.2, R34.2, U1.3 (SW)
unnamed: C57.1, R27.1, U1.1 (VIN)
PGND: C54.2, C55.2, C56.2, C60.2, C61.2, C62.2, Q2.1 (S), Q2.2 (S), Q2.3 (S), R26.2, R32.2, R196.2, T2.2, TP5.1 (1_1), U1.6 (NC), U1.7 (NC), U1.13 (NC), U1.14 (NC), U1.15 (NC), U1.17 (EPAD)
VBUS: F1.1; also elsewhere on the board

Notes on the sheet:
Connect at U1 Pins 16-17
Uen=1V Uon=12V
15V

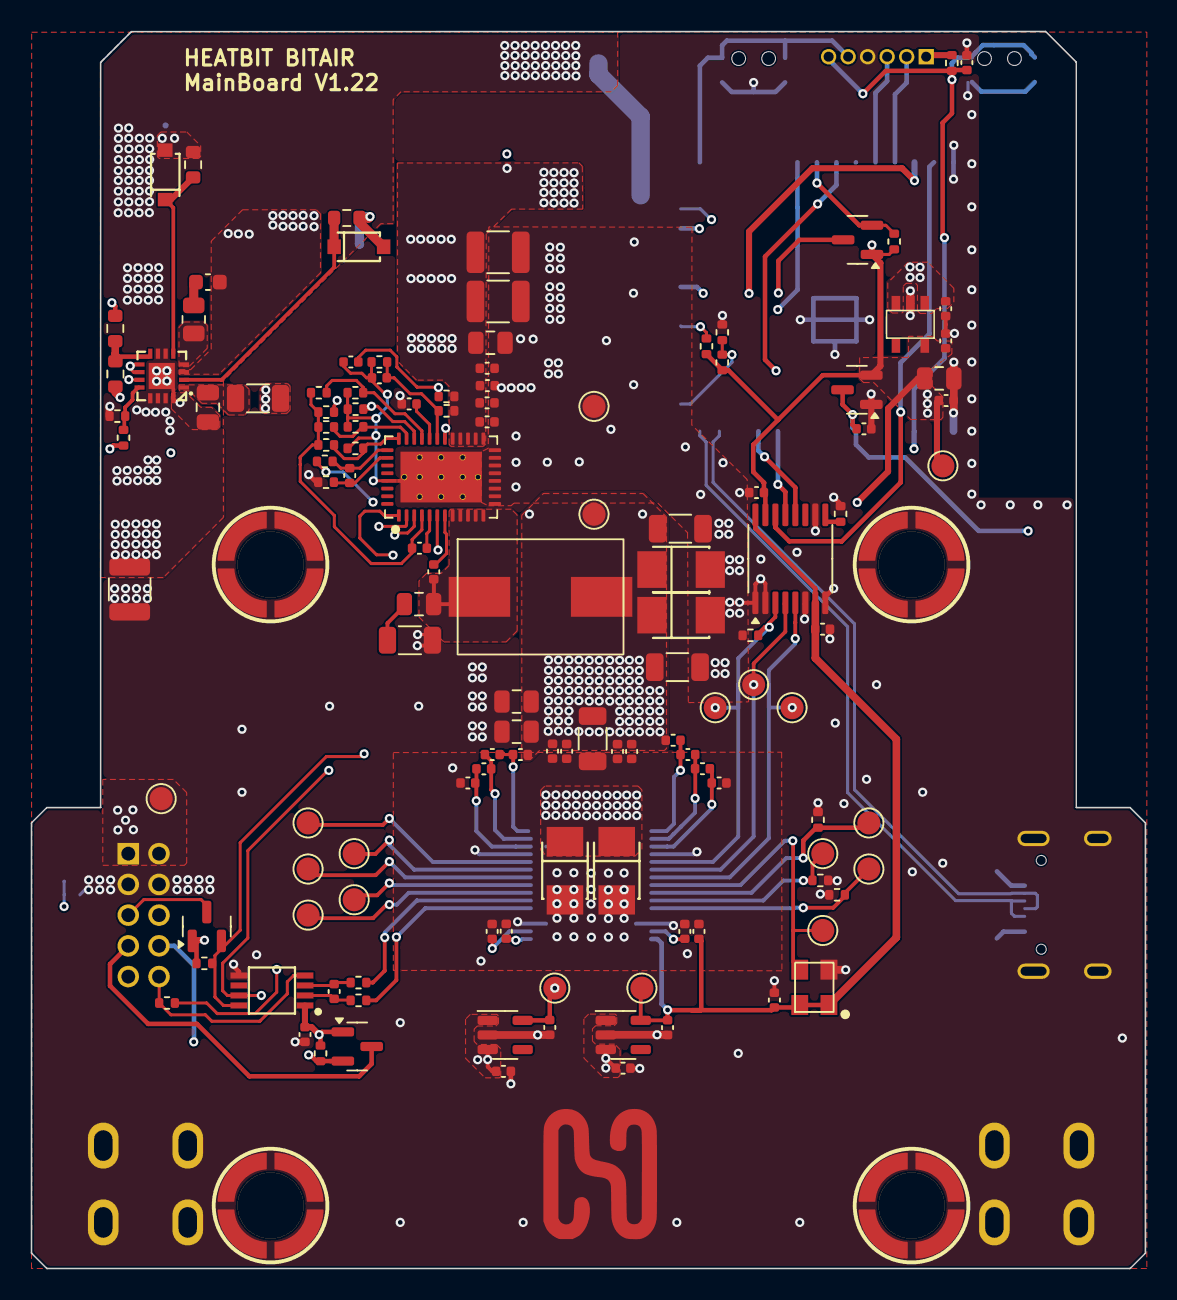
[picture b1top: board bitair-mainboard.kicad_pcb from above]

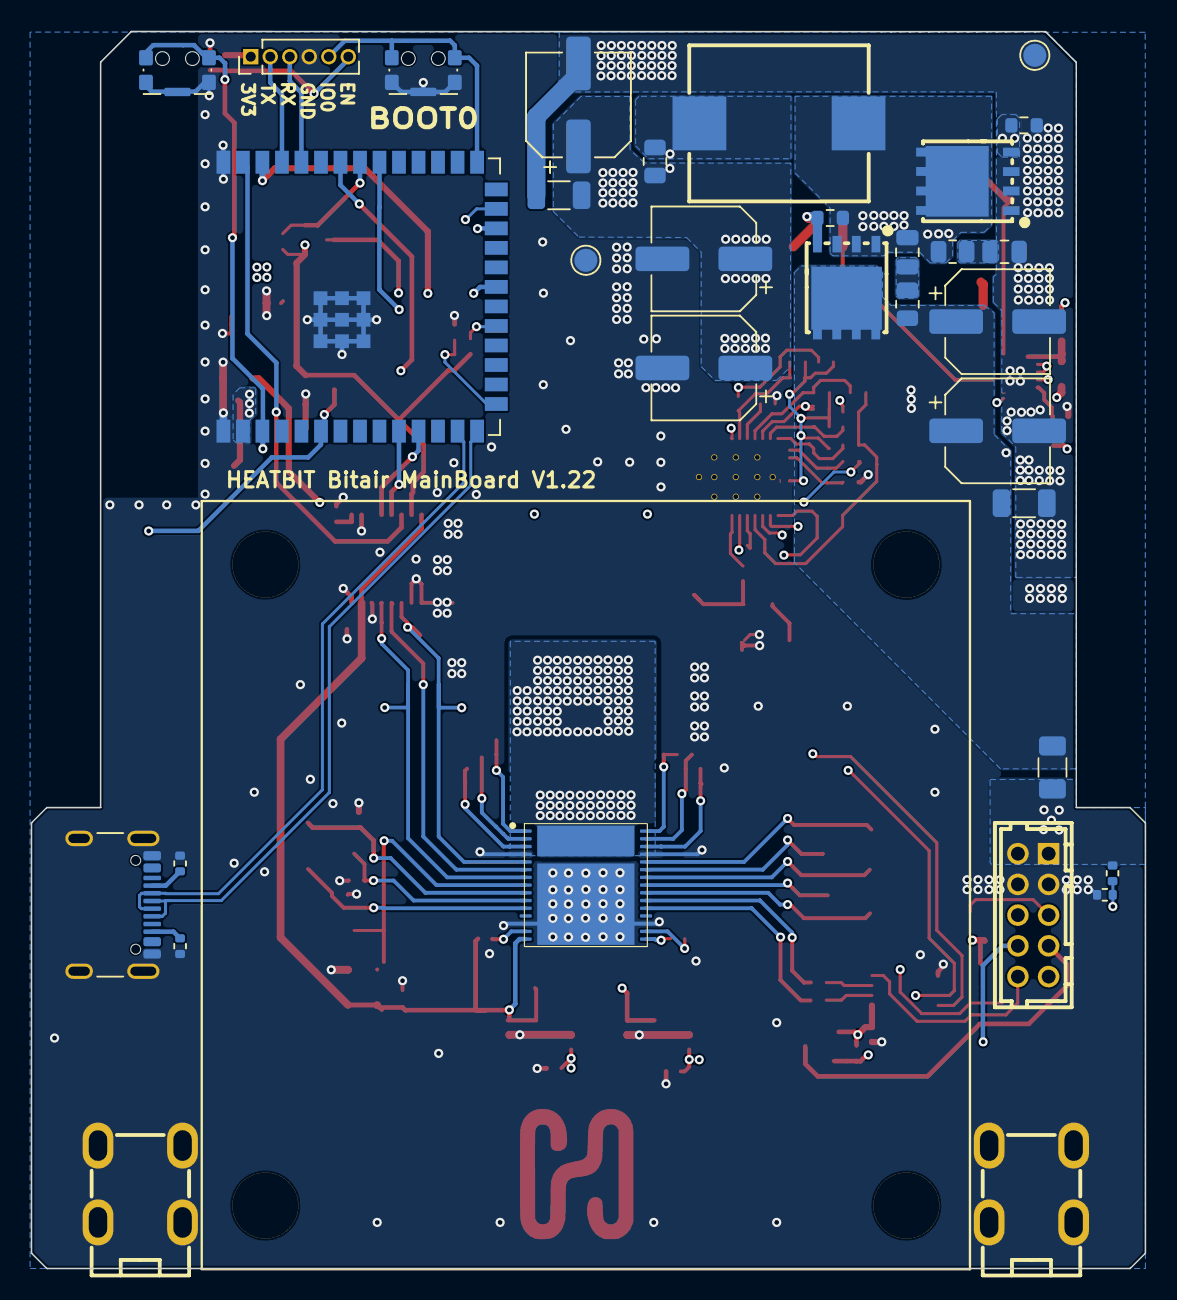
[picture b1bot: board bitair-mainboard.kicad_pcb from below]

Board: 4 copper layers, 72.5 x 80.5 mm, 166 parts (33 on the bottom side), 87 nets.

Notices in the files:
Power_15_5.kicad_sch:
Based on bitaxeGamma (c) 2024-2025 bitaxeorg, github.com/bitaxeorg/bitaxeGamma
Modifications (c) 2026 Heatbit Inc. See NOTICE.md for the list of changes
Licensed under CERN-OHL-S-2.0 (see LICENSE)
